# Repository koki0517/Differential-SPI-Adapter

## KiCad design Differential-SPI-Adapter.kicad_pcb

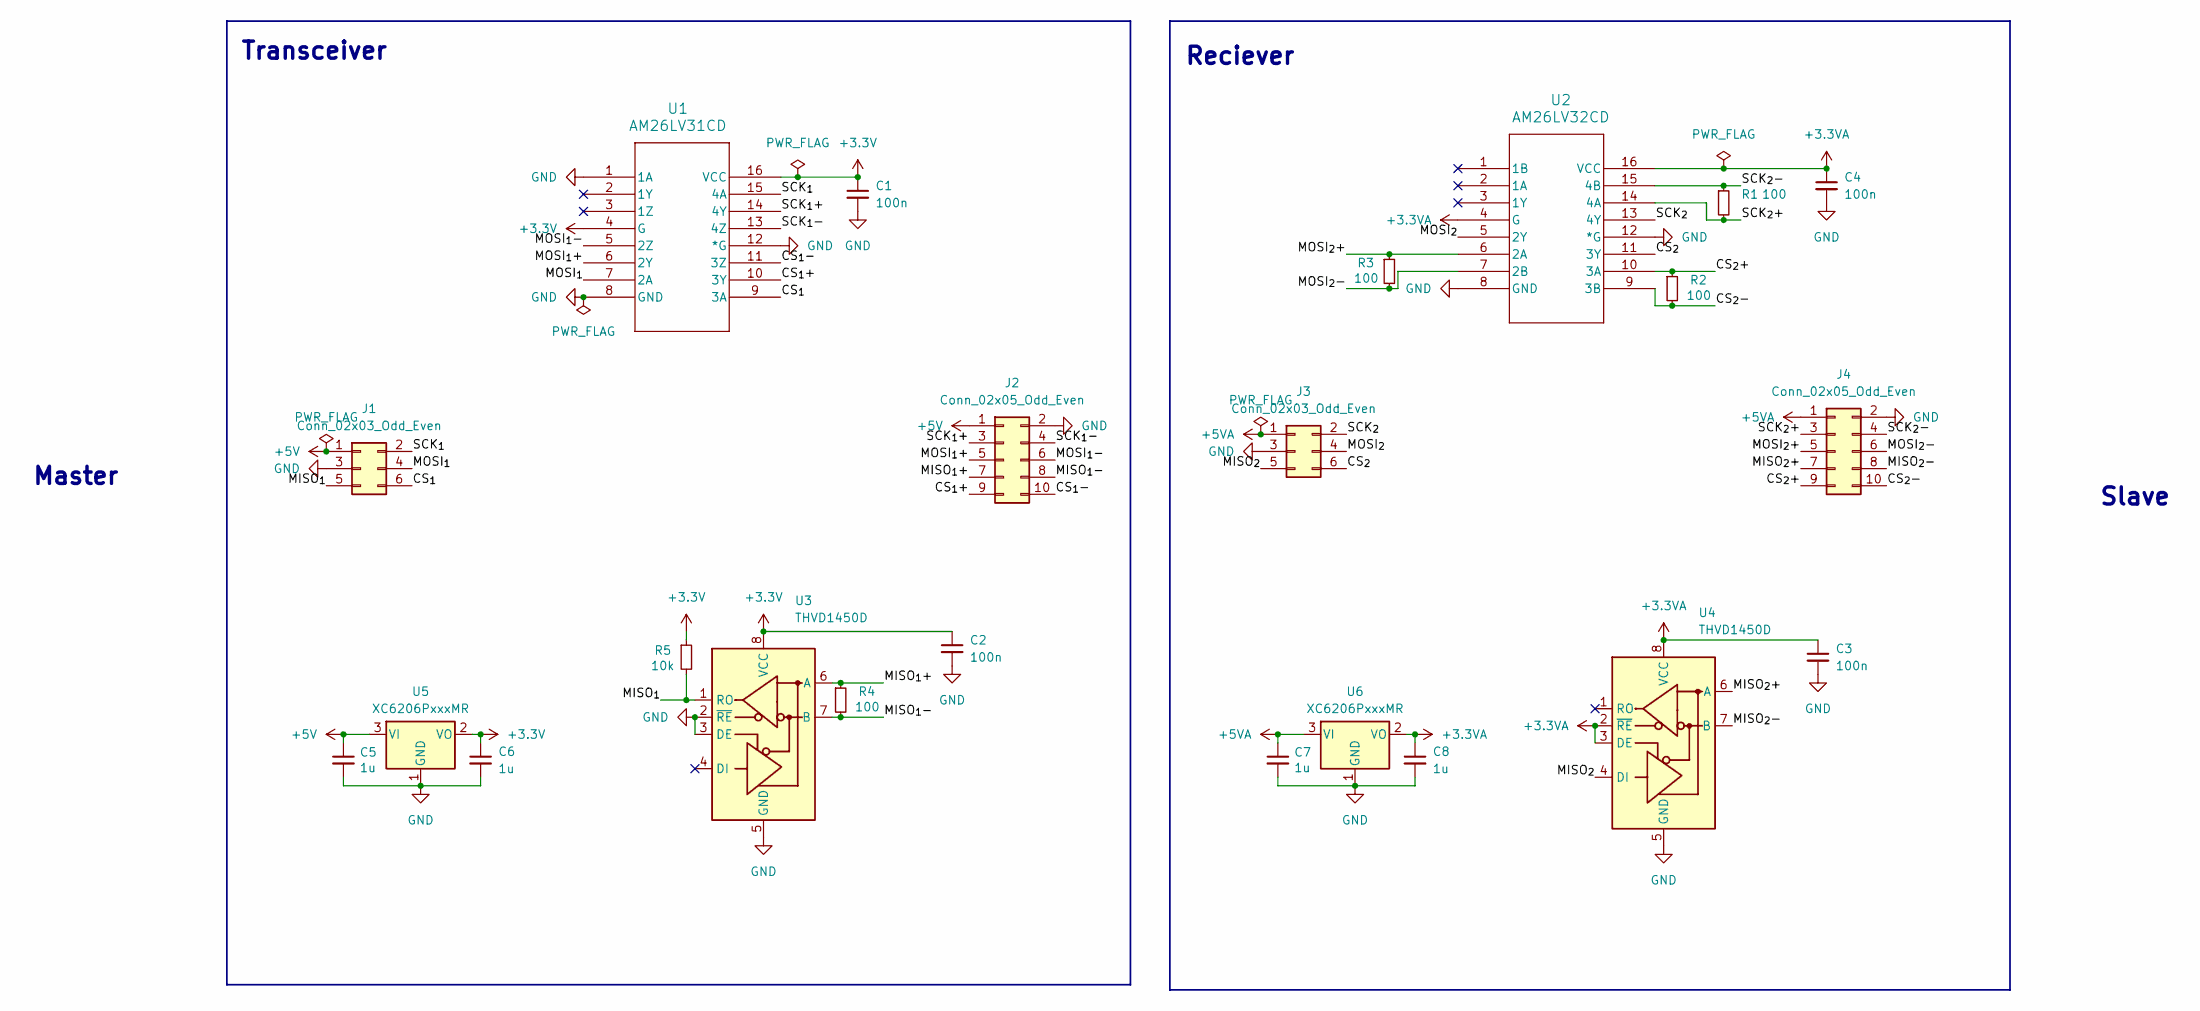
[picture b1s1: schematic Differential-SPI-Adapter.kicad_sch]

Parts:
C1, C2, C3, C4: 100n; C_0603_1608Metric_Pad1.08x0.95mm_HandSolder
C5, C6, C7, C8: 1u; C_0603_1608Metric_Pad1.08x0.95mm_HandSolder
J1, J3: Conn_02x03_Odd_Even; IDC-Header_2x03_P2.54mm_Horizontal
J2, J4: Conn_02x05_Odd_Even; IDC-Header_2x05_P2.54mm_Horizontal
R1, R2, R3, R4: 100; R_0603_1608Metric_Pad0.98x0.95mm_HandSolder
R5: 10k; R_0603_1608Metric_Pad0.98x0.95mm_HandSolder
U1: AM26LV31CD; D16
U2: AM26LV32CD; D16
U3, U4: THVD1450D; SOIC-8_3.9x4.9mm_P1.27mm
U5, U6: XC6206PxxxMR; SOT-89-3_Handsoldering; LCSC C5446

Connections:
+3.3V: C1.1, C2.1, C6.1, R5.1, U1.4 (G), U1.16 (VCC), U3.8 (VCC), U5.2 (VO)
+3.3VA: C3.1, C4.1, C8.1, U2.4 (G), U2.16 (VCC), U4.2 (~RE), U4.3 (DE), U4.8 (VCC), U6.2 (VO)
+5V: C5.1, J1.1, J2.1, U5.3 (VI)
+5VA: C7.1, J3.1, J4.1, U6.3 (VI)
/CS_{1}: J1.6, U1.9 (3A)
/CS_{1}+: J2.9, U1.10 (3Y)
/CS_{1}-: J2.10, U1.11 (3Z)
/CS_{2}: J3.6, U2.11 (3Y)
/CS_{2}+: J4.9, R2.1, U2.10 (3A)
/CS_{2}-: J4.10, R2.2, U2.9 (3B)
/MISO_{1}: J1.5, R5.2, U3.1 (RO)
/MISO_{1}+: J2.7, R4.1, U3.6 (A)
/MISO_{1}-: J2.8, R4.2, U3.7 (B)
/MISO_{2}: J3.5, U4.4 (DI)
/MISO_{2}+: J4.7, U4.6 (A)
/MISO_{2}-: J4.8, U4.7 (B)
/MOSI_{1}: J1.4, U1.7 (2A)
/MOSI_{1}+: J2.5, U1.6 (2Y)
/MOSI_{1}-: J2.6, U1.5 (2Z)
/MOSI_{2}: J3.4, U2.5 (2Y)
/MOSI_{2}+: J4.5, R3.1, U2.6 (2A)
/MOSI_{2}-: J4.6, R3.2, U2.7 (2B)
/SCK_{1}: J1.2, U1.15 (4A)
/SCK_{1}+: J2.3, U1.14 (4Y)
/SCK_{1}-: J2.4, U1.13 (4Z)
/SCK_{2}: J3.2, U2.13 (4Y)
/SCK_{2}+: J4.3, R1.2, U2.14 (4A)
/SCK_{2}-: J4.4, R1.1, U2.15 (4B)
GND: C1.2, C2.2, C3.2, C4.2, C5.2, C6.2, C7.2, C8.2, J1.3, J2.2, J3.3, J4.2, U1.1 (1A), U1.8 (GND), U1.12 (*G), U2.8 (GND), U2.12 (*G), U3.2 (~RE), U3.3 (DE), U3.5 (GND), U4.5 (GND), U5.1 (GND), U6.1 (GND)

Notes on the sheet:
Slave
Master
Reciever
Transceiver

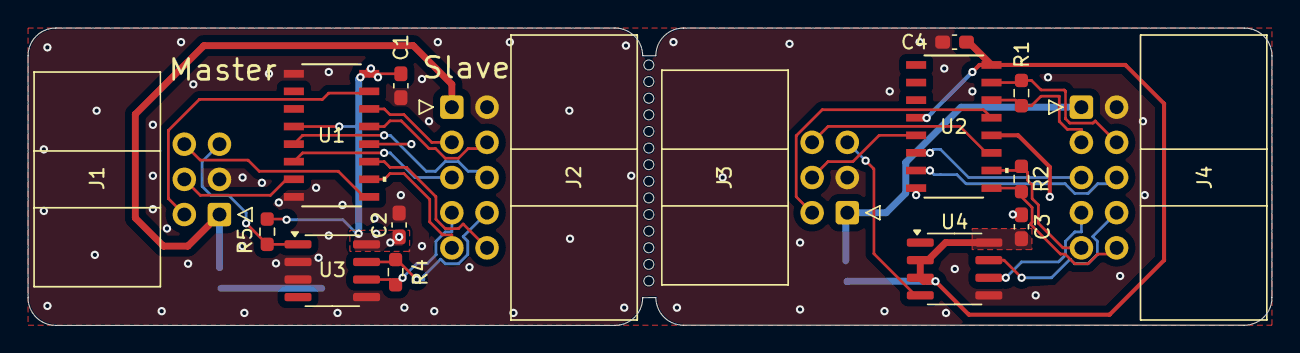
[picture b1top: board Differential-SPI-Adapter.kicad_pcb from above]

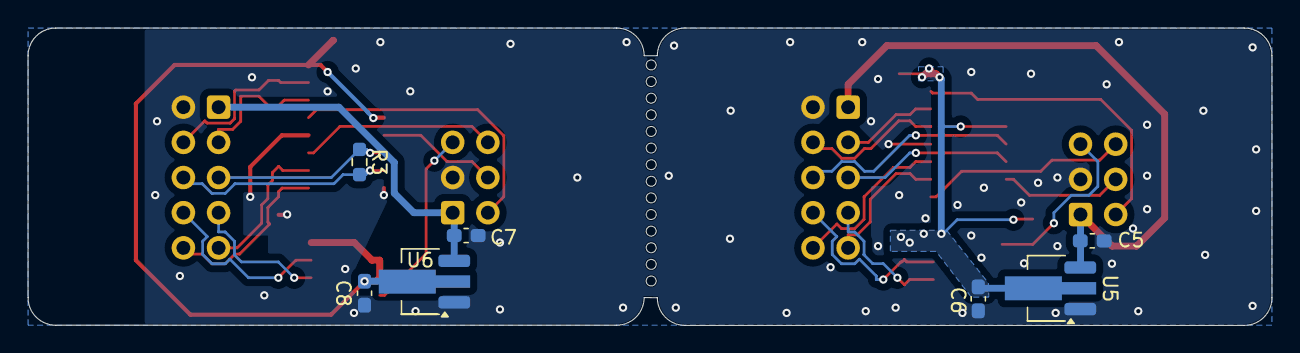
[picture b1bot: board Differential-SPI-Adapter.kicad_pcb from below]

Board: 2 copper layers, 89.8 x 21.5 mm, 23 parts (7 on the bottom side), 29 nets.

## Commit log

2025-11-24 Add linence
2025-11-24 kicadファイルの作成
2025-11-25 add references
2025-11-30 Transceiver
2025-12-14 reciever
2025-12-14 fix transceiver
